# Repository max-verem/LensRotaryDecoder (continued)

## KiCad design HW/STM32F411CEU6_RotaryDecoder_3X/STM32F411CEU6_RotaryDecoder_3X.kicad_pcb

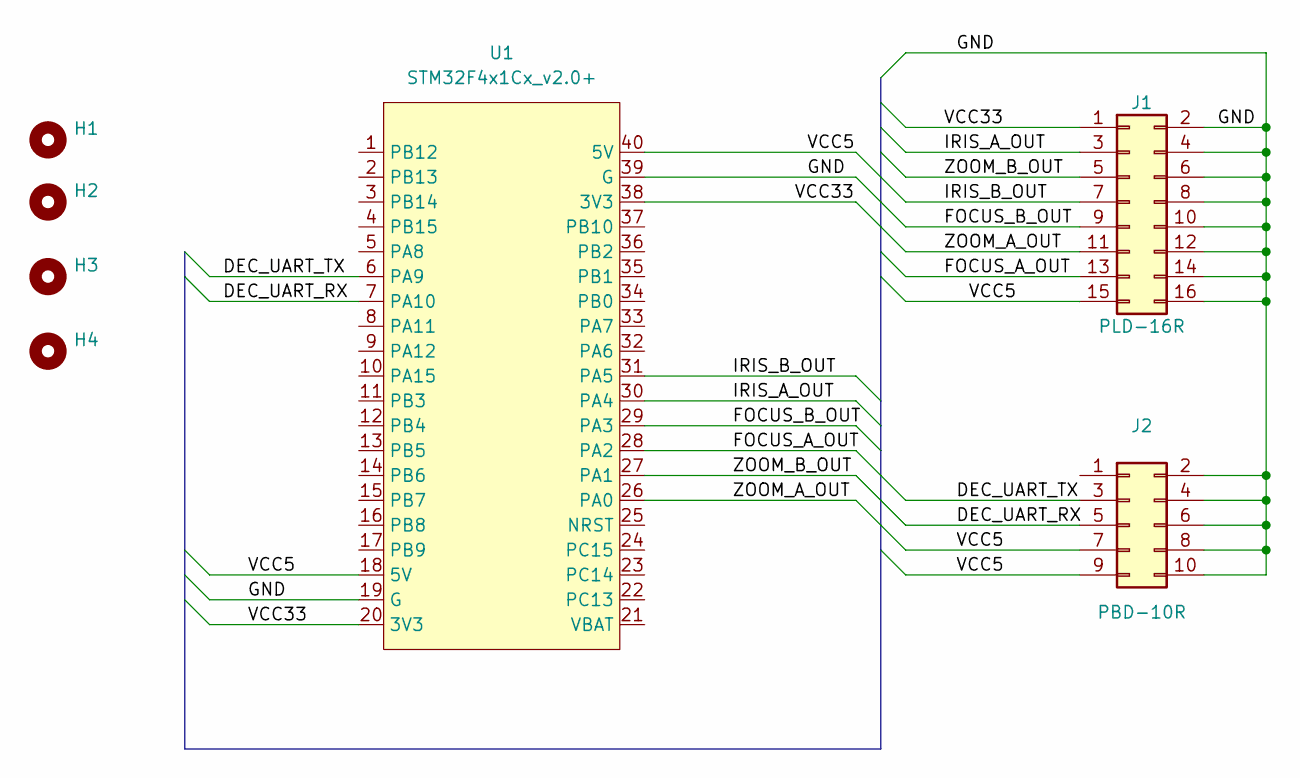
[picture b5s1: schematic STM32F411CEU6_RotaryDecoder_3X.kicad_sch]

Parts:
H1, H2, H3, H4: MountingHole; MountingHole_3.2mm_M3
J1: PLD-16R; PinHeader_2x08_P2.54mm_Horizontal
J2: PBD-10R; PinSocket_2x05_P2.54mm_Horizontal
U1: STM32F4x1Cx_v2.0+; DIP-40_W15.24mm_LongPads

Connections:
/DEC_UART_RX: J2.5, U1.7 (PA10)
/DEC_UART_TX: J2.3, U1.6 (PA9)
/FOCUS_A_OUT: J1.13, U1.28 (PA2)
/FOCUS_B_OUT: J1.9, U1.29 (PA3)
/GND: J1.2, J1.4, J1.6, J1.8, J1.10, J1.12, J1.14, J1.16, J2.2, J2.4, J2.6, J2.8, J2.10, U1.19 (G), U1.39 (G)
/IRIS_A_OUT: J1.3, U1.30 (PA4)
/IRIS_B_OUT: J1.7, U1.31 (PA5)
/VCC5: J1.15, J2.7, J2.9, U1.18 (5V), U1.40 (5V)
/VCC33: J1.1, U1.20 (3V3), U1.38 (3V3)
/ZOOM_A_OUT: J1.11, U1.26 (PA0)
/ZOOM_B_OUT: J1.5, U1.27 (PA1)

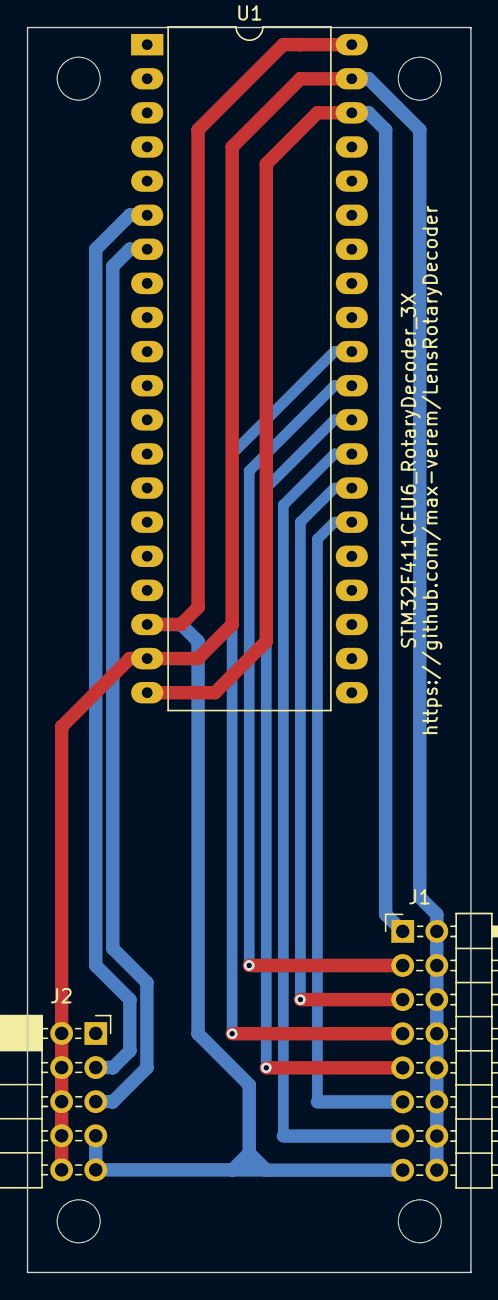
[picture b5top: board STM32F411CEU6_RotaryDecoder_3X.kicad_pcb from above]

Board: 2 copper layers, 33.0 x 92.7 mm, 7 parts (0 on the bottom side), 11 nets.

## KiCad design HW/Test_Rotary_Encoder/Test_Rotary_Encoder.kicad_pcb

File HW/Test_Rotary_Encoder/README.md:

# Test Rotary Encoder

This is a EC11 rotary encoder with debouncing curcuit that is used in this project to debug and simulating purpose.

## Main module

## Schematic

## PCB

gerber [file](gerber/)

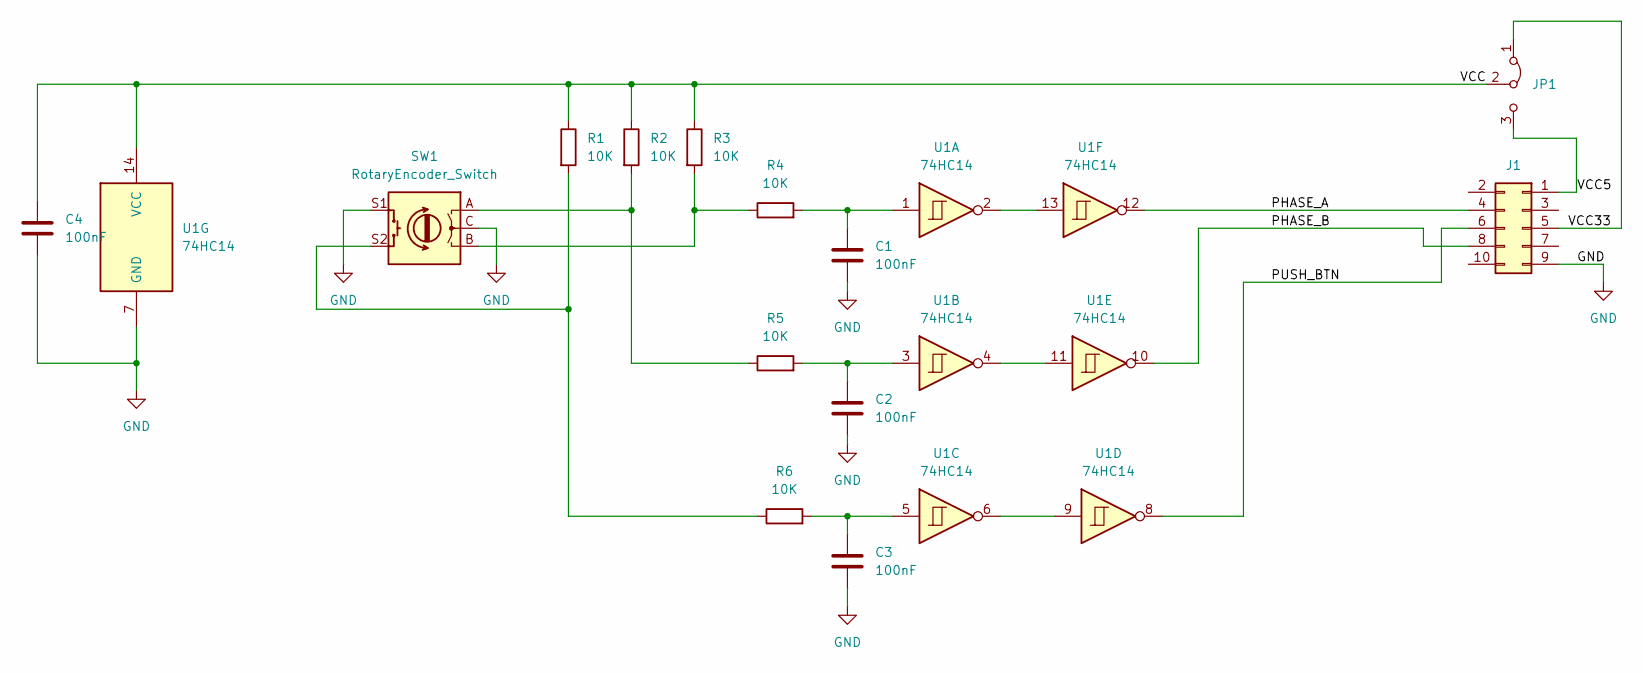
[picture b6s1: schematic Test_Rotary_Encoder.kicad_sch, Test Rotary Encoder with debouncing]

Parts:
C1, C2, C3, C4: 100nF; C_Rect_L7.0mm_W2.0mm_P5.00mm
J1: Conn_02x05_Odd_Even; IDC-Header_2x05_P2.54mm_Vertical
JP1: Jumper_3_Bridged12; PinHeader_1x03_P2.54mm_Vertical
R1, R2, R3, R4, R5, R6: 10K; R_Axial_DIN0309_L9.0mm_D3.2mm_P12.70mm_Horizontal
SW1: RotaryEncoder_Switch; RotaryEncoder_Alps_EC11E-Switch_Vertical_H20mm
U1: 74HC14; DIP-14_W7.62mm

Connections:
/PHASE_A: J1.4, U1.12
/PHASE_B: J1.8, U1.10
/PUSH_BTN: J1.6, U1.8
/VCC: C4.1, JP1.2 (C), R1.1, R2.1, R3.1, U1.14 (VCC)
/VCC5: J1.1, JP1.3 (B)
/VCC33: J1.5, JP1.1 (A)
GND: C1.2, C2.2, C3.2, C4.2, J1.9, SW1.C, SW1.S1, U1.7 (GND)
unnamed: C1.1, R4.2, U1.1
unnamed: C2.1, R5.2, U1.3
unnamed: C3.1, R6.2, U1.5
unnamed: R1.2, R6.1, SW1.S2
unnamed: R2.2, R5.1, SW1.A
unnamed: R3.2, R4.1, SW1.B
unnamed: U1.6, U1.9
unnamed: U1.4, U1.11
unnamed: U1.2, U1.13

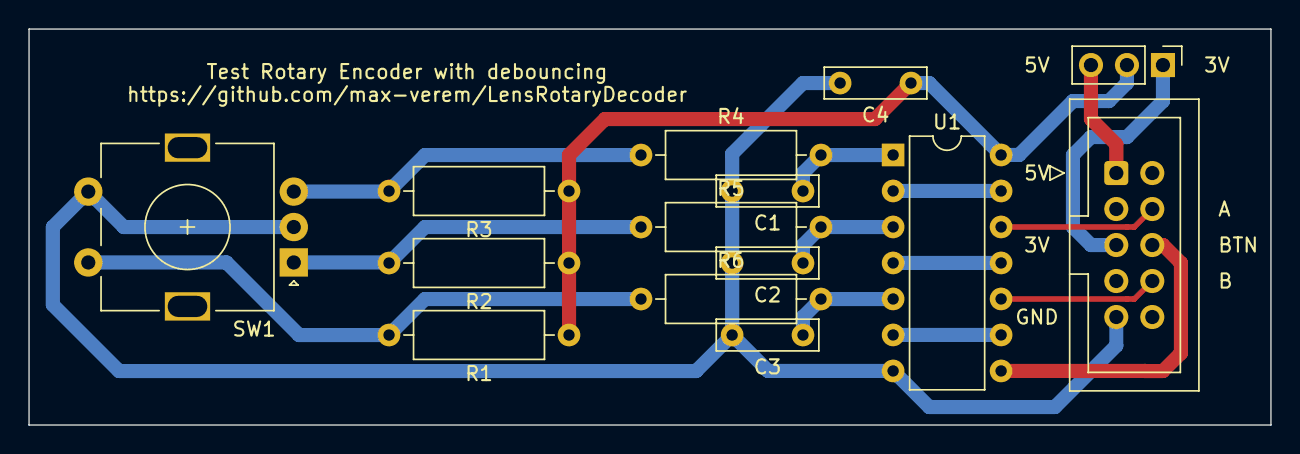
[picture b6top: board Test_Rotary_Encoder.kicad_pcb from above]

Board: 2 copper layers, 87.6 x 27.9 mm, 14 parts (0 on the bottom side), 16 nets.

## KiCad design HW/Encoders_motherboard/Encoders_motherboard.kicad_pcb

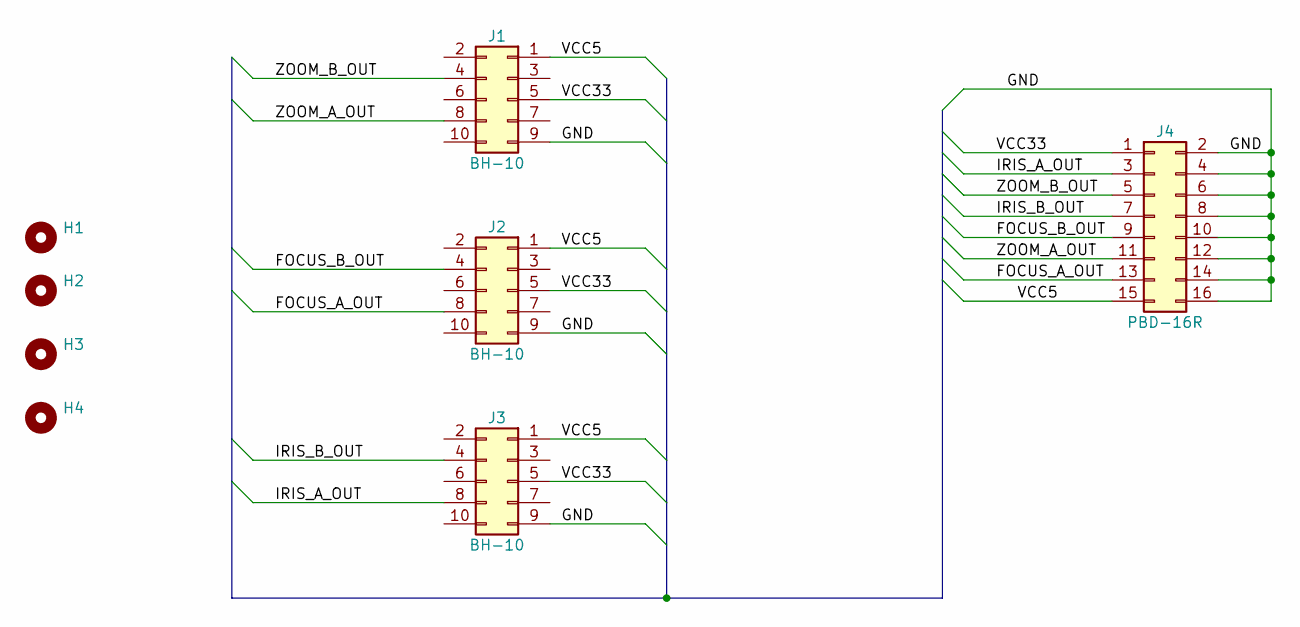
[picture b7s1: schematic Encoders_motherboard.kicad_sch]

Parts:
H1, H2, H3, H4: MountingHole; MountingHole_3.2mm_M3
J1, J2, J3: BH-10; IDC-Header_2x05_P2.54mm_Vertical
J4: PBD-16R; PinSocket_2x08_P2.54mm_Horizontal

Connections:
/FOCUS_A_OUT: J2.8, J4.13
/FOCUS_B_OUT: J2.4, J4.9
/GND: J1.9, J2.9, J3.9, J4.2, J4.4, J4.6, J4.8, J4.10, J4.12, J4.14, J4.16
/IRIS_A_OUT: J3.8, J4.3
/IRIS_B_OUT: J3.4, J4.7
/VCC5: J1.1, J2.1, J3.1, J4.15
/VCC33: J1.5, J2.5, J3.5, J4.1
/ZOOM_A_OUT: J1.8, J4.11
/ZOOM_B_OUT: J1.4, J4.5

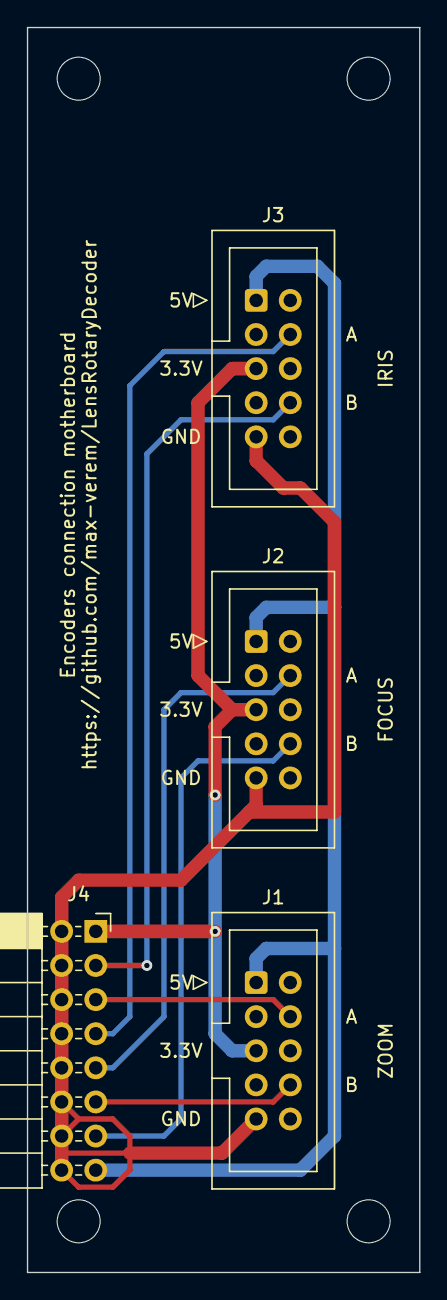
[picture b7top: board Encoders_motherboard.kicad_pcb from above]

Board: 2 copper layers, 29.2 x 92.7 mm, 8 parts (0 on the bottom side), 9 nets.

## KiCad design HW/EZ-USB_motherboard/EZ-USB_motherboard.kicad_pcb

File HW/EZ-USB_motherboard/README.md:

# EZ-USB (CY7C68013A EZ-USB FX2LP) based decoder board for Canon HJ14ex4.3B IRSE 

## Schematic

## PCB

## GERBER
You can download [gerber archive here](gerber/)

## Final board

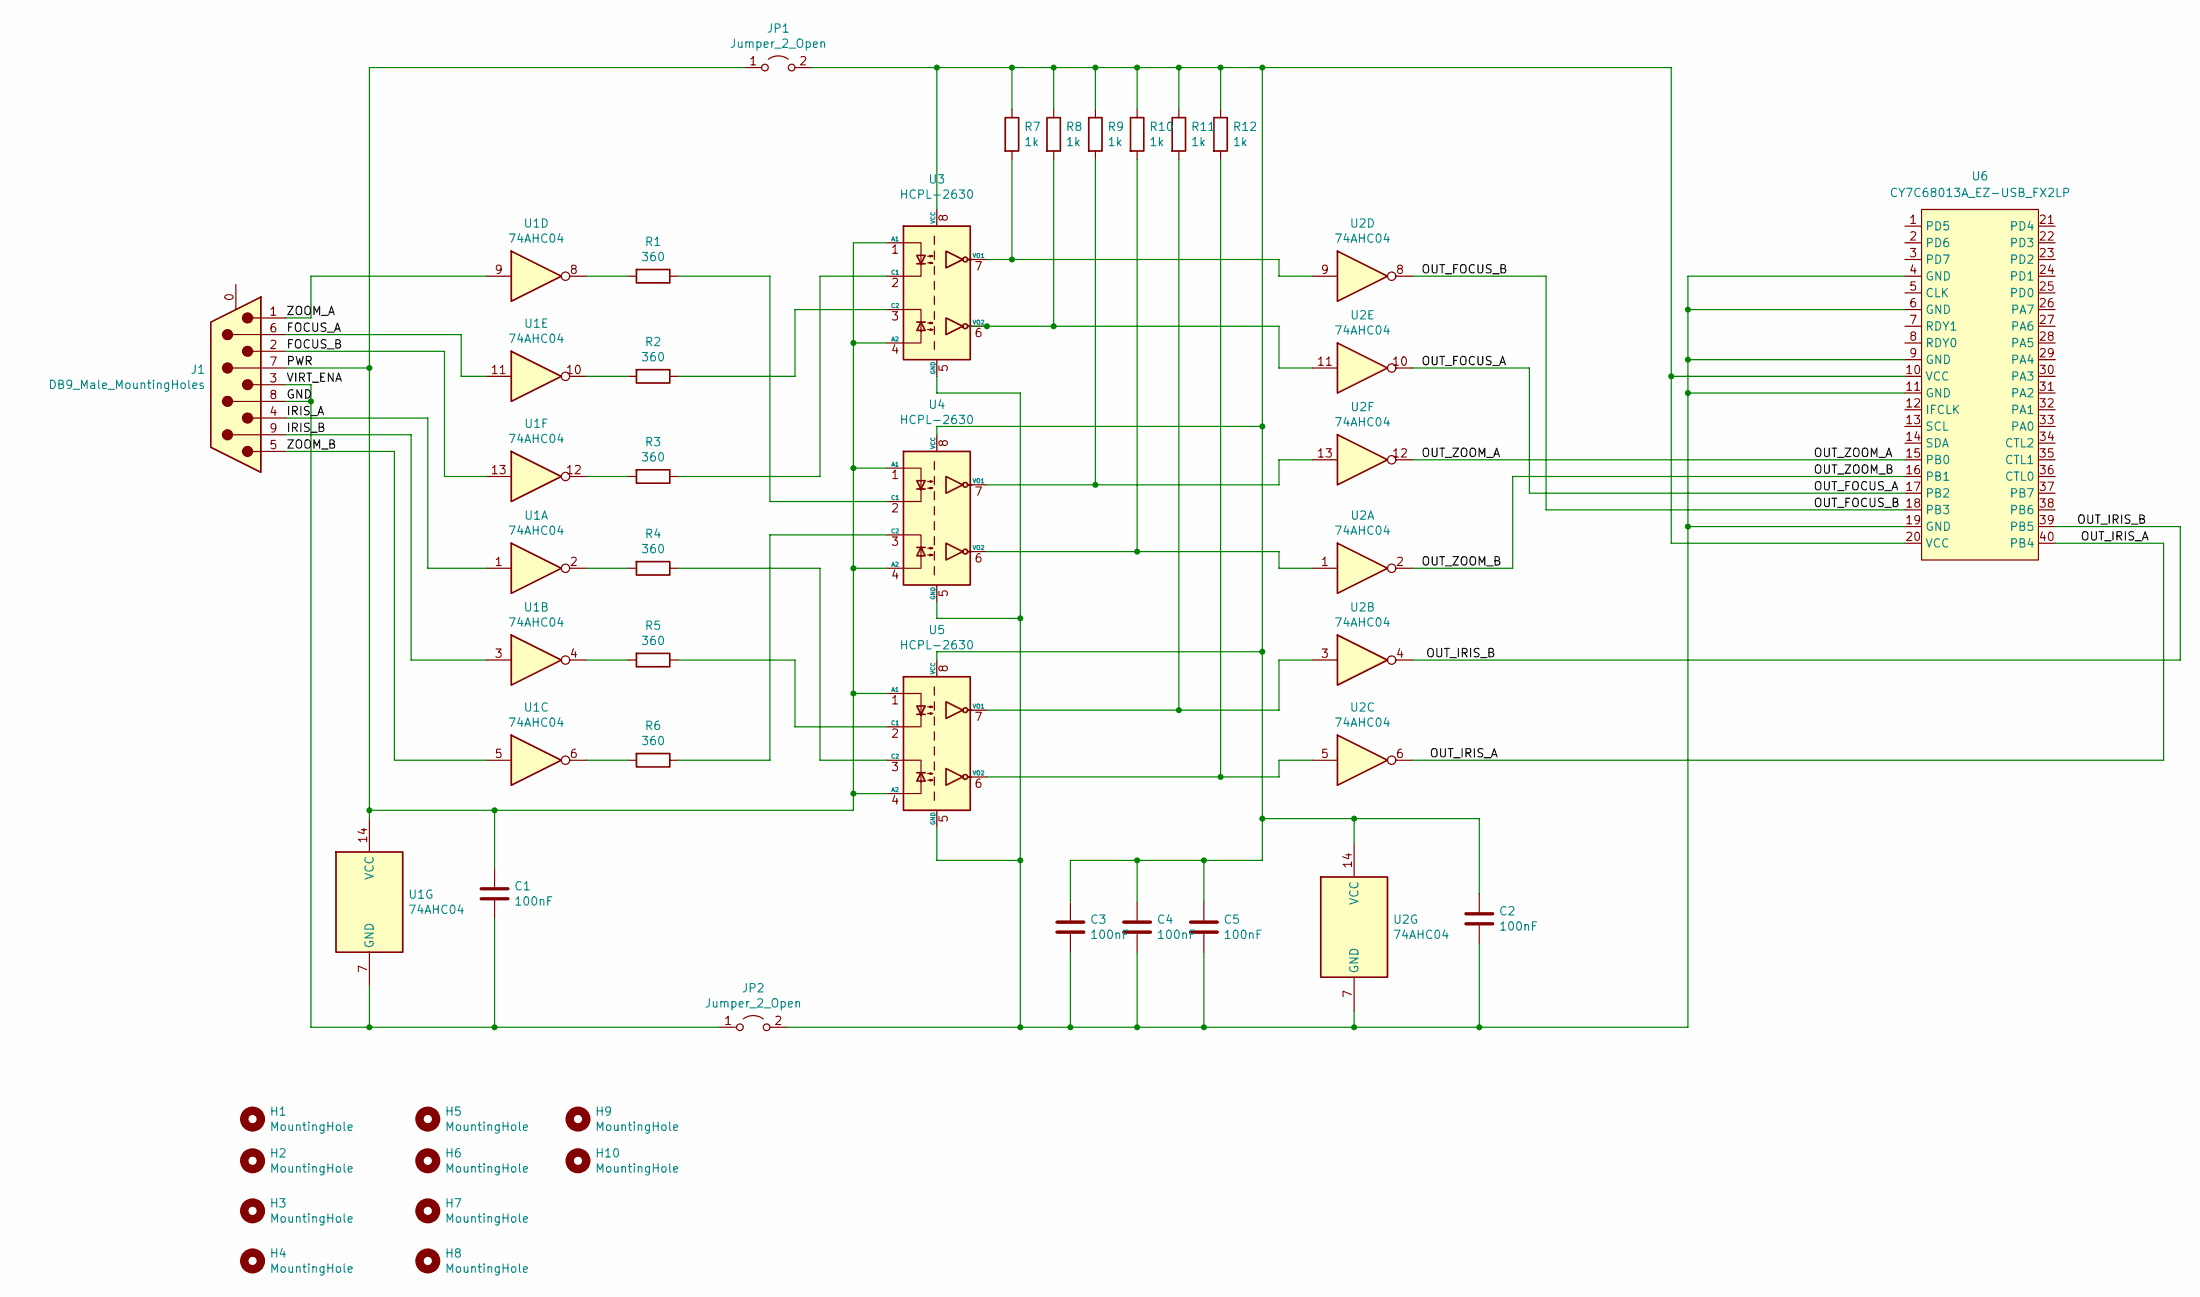
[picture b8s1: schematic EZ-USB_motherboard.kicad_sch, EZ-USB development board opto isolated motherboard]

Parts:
C1, C2, C3, C4, C5: 100nF; C_Rect_L7.0mm_W2.0mm_P5.00mm
H1, H2, H3, H4, H5, H6, H7, H8, H9, H10: MountingHole; MountingHole_3.2mm_M3
J1: DB9_Male_MountingHoles; DSUB-9_Male_Horizontal_P2.77x2.84mm_EdgePinOffset9.90mm_Hou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
JP1, JP2: Jumper_2_Open; PinHeader_1x02_P2.54mm_Vertical
R1, R2, R3, R4, R5, R6: 360; R_Axial_DIN0309_L9.0mm_D3.2mm_P12.70mm_Horizontal
R7, R8, R9, R10, R11, R12: 1k; R_Axial_DIN0309_L9.0mm_D3.2mm_P12.70mm_Horizontal
U1, U2: 74AHC04; DIP-14_W7.62mm
U3, U4, U5: HCPL-2630; DIP-8_W7.62mm
U6: CY7C68013A_EZ-USB_FX2LP

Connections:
/FOCUS_A: J1.6, U1.11
/FOCUS_B: J1.2, U1.13
/GND: C1.2, J1.3, J1.8, JP2.1 (A), U1.7 (GND)
/IRIS_A: J1.4, U1.1
/IRIS_B: J1.9, U1.3
/OUT_FOCUS_A: U2.10, U6.17 (PB2)
/OUT_FOCUS_B: U2.8, U6.18 (PB3)
/OUT_IRIS_A: U2.6, U6.40 (PB4)
/OUT_IRIS_B: U2.4, U6.39 (PB5)
/OUT_ZOOM_A: U2.12, U6.15 (PB0)
/OUT_ZOOM_B: U2.2, U6.16 (PB1)
/PWR: C1.1, J1.7, JP1.1 (A), U1.14 (VCC), U3.1 (A1), U3.4 (A2), U4.1 (A1), U4.4 (A2), U5.1 (A1), U5.4 (A2)
/ZOOM_A: J1.1, U1.9
/ZOOM_B: J1.5, U1.5
unnamed: C2.1, C3.1, C4.1, C5.1, JP1.2 (B), R7.1, R8.1, R9.1, R10.1, R11.1, R12.1, U2.14 (VCC), U3.8 (VCC), U4.8 (VCC), U5.8 (VCC), U6.10 (VCC), U6.20 (VCC)
unnamed: C2.2, C3.2, C4.2, C5.2, JP2.2 (B), U2.7 (GND), U3.5 (GND), U4.5 (GND), U5.5 (GND), U6.4 (GND), U6.6 (GND), U6.9 (GND), U6.11 (GND), U6.19 (GND)
unnamed: R1.1, U4.2 (C1)
unnamed: R1.2, U1.8
unnamed: R2.1, U3.3 (C2)
unnamed: R2.2, U1.10
unnamed: R3.1, U3.2 (C1)
unnamed: R3.2, U1.12
unnamed: R4.1, U5.3 (C2)
unnamed: R4.2, U1.2
unnamed: R5.1, U5.2 (C1)
unnamed: R5.2, U1.4
unnamed: R6.1, U4.3 (C2)
unnamed: R6.2, U1.6
unnamed: R7.2, U2.9, U3.7 (VO1)
unnamed: R8.2, U2.11, U3.6 (VO2)
unnamed: R9.2, U2.13, U4.7 (VO1)
unnamed: R10.2, U2.1, U4.6 (VO2)
unnamed: R11.2, U2.3, U5.7 (VO1)
unnamed: R12.2, U2.5, U5.6 (VO2)

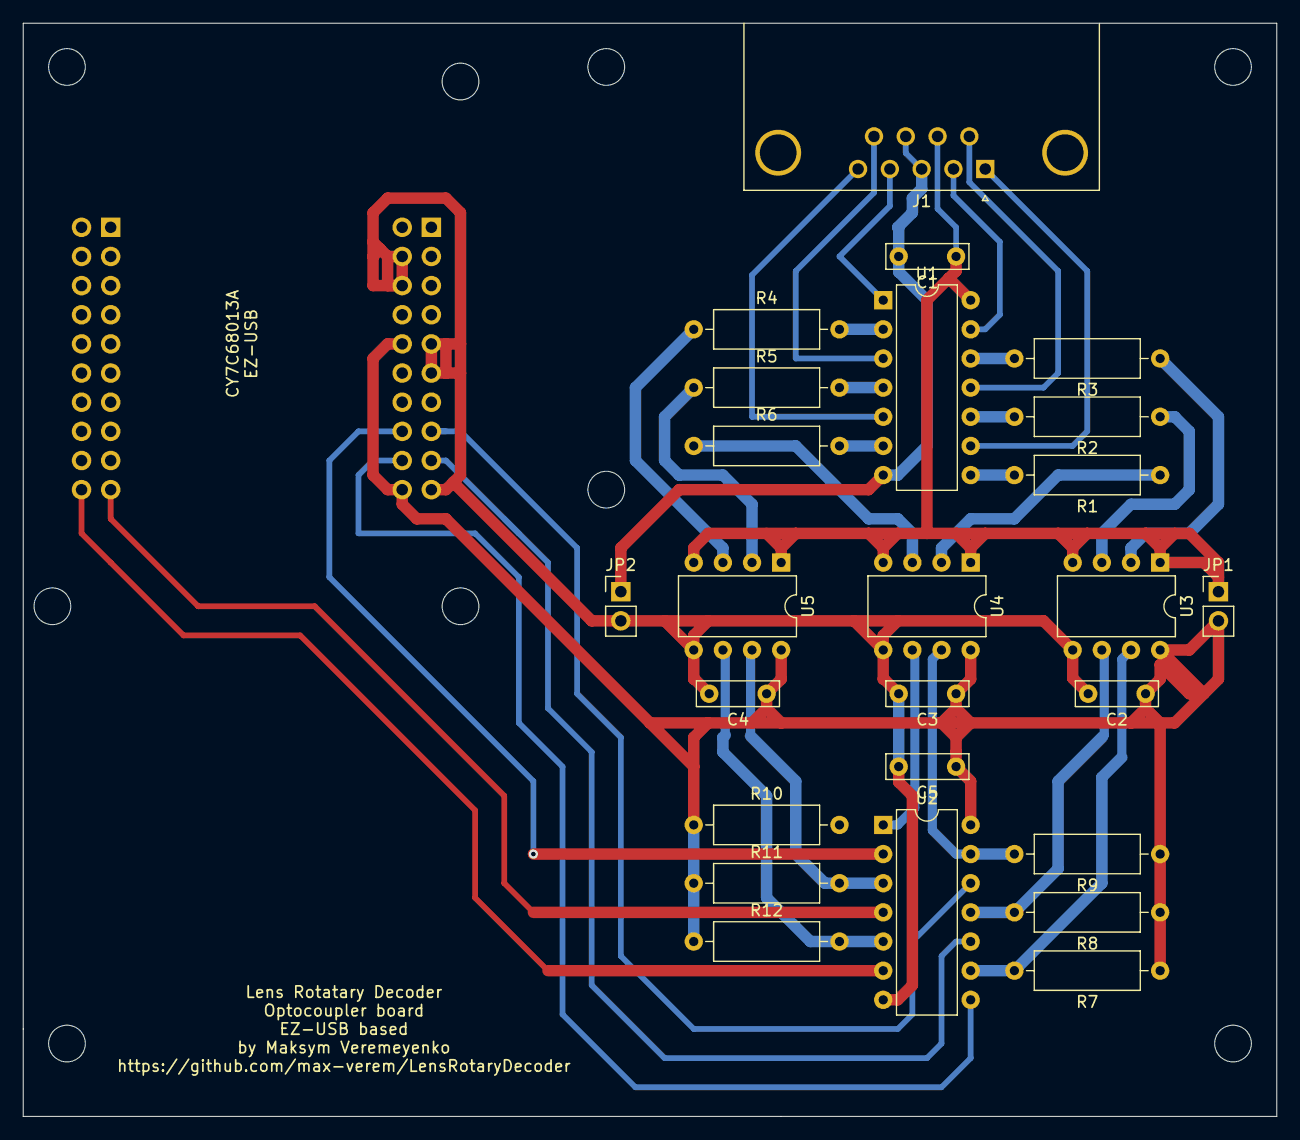
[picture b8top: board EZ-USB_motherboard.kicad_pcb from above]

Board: 2 copper layers, 109.2 x 95.2 mm, 36 parts (1 on the bottom side), 34 nets.

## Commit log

2021-10-12 Initial source code load
2021-10-13 Update CUSTOM_HID_EPIN_SIZE/CUSTOM_HID_EPOUT_SIZE constant to 64
2021-10-13 Update CUSTOM_HID_ReportDesc_FS (reports descriptor)
2021-10-13 Incorporate old working code
2021-10-13 Add .gitignore
2021-10-13 Fix setting initial value byte order
2021-10-13 Clone project for STM32F411CEU6 mcu
2021-10-13 Ignore Debug folder
2021-10-13 Revert byte order change
2021-10-26 FPGA rotary decoder skeleton
2021-12-14 Add EZ-USB rotary decoder skeleton
2021-12-15 Add 'common' code
2021-12-15 Implement minimal reader
2021-12-24 re-implement rotatry decoder
2021-12-24 decoder1 scheme/pcb added
2021-12-24 Re-organize directories for pcb/schematic
2021-12-30 Enable pullup resistors on STM's pins
2021-12-30 add stm32 rotary decoder skeleton
2021-12-30 Implement getting rotary decoder data from STM32 usb dongle
2021-12-30 Update USB VID/PID
2021-12-30 Modify counter/packet length
2022-01-04 MojoV3 serial reader skeleton added
2022-01-04 Implement packet decoder for MojoV3
2022-01-04 FPGA skeleton added
2022-01-04 Basic MojoV3 project added
2022-01-04 Implement static packet serial sender
2022-01-04 Integrate existing Verilog rotary decoder
2022-01-04 Fix byte order
2022-01-04 Integrate EPM570 Verilog code
2022-01-04 Add serial sender module to EPM570 code
2022-01-04 Rename STM32 projects
2022-01-04 Cleanup STM32 projects tree
2022-01-04 Cleanup STM32 projects tree, prepare new project tree
2022-01-04 Add UART code to STM32 project
2022-01-04 Implement serial receive from FPGA, rise frequencies
2022-01-05 uart HAL_Drivers added
2022-01-05 Set 250000 baud output speed for EPM570
2022-01-05 Implement decoding bytestream from EPM570
2022-01-05 Bypass all UART bytestream to HID
2022-01-05 Convert Schematic/PCB to KiCad6.0 format
2022-01-05 Add Kicad-STM32 module for schematic projects
2022-01-05 Camera Lens Cable schematic added
2022-01-05 Update STM32 clock generation config
2022-01-06 Enable timers and dma for futher tests
2022-01-06 Save performance test code
2022-01-06 Rename STM32 project: F411 would be 3X rotation decoder
2022-01-06 Clone and rename stm32_rot_dec into two different reader for compatibility
2022-01-06 rename STM32F103C8_RotaryDecoder to STM32F103C8_RotaryDecoder_1X
2022-01-06 Update Decoders product string
2022-01-06 Fix STM32 decoders projects split
2022-01-06 Cleanup STM32F411CEU6_RotaryDecoder_3X project
2022-01-06 DMA GPIO reading skeleton
2022-01-07 Use DMA2 and TIM1 for getting GPIOA
2022-01-07 Implement getting statistic data
2022-01-07 Test rotary encoder schematic/pcb added
2022-01-07 Update MojoV3's fpga pins for Mojo Hat compatibility
2022-01-11 Implement table based STM32 rotary decoder
2022-01-11 Prevent app crashing after unplug usb dongle
2022-01-11 Cleanup STM32 decoder code, specify constants for table and calc based algorithms
2022-01-12 Initial UART code support added
2022-01-12 Add new modules for STM-UART project
2022-01-13 second OLED display added
2022-01-14 Implement deciminal convertion
2022-01-14 Implement signed/unsigned to decinimal convertion
2022-01-14 I2C to 40000, DMA FIFO, Burst mode
2022-01-14 Sync EZ-USB based decoder to latest version
2022-01-17 UART output startup added
2022-01-17 Rework packet header, enable fifo and burst mode
2022-01-17 Rework packet format
2022-01-17 Sync schematic and pcb with git head
2022-01-18 Restore timer setting throw contstants
2022-01-18 Fix storing status after packet format change
2022-01-18 Link with W5500 library
2022-01-19 UART to NET skeleton
2022-01-19 Minimal UDP sender skeleton for STM32
2022-01-19 Add forgoten files of EPM570 FPGA decoder
2022-01-19 Enable IRQ for UART, setup 230400 baudrate
2022-01-20 Implement Free-D UDP packet sending
2022-01-20 Save some obsolete projects
2022-01-21 Add schematic and pcb of decoder with OLED and NET support
2022-01-21 Enable SPI2 for testing
2022-01-21 Add macros to select SPI used for W5500
2022-01-24 Implement Free-D packet sending
2022-01-25 Fix syncing thread of ez-usb reader
2022-01-25 Add options description for stm32_rot_dec_3x1 reader
2022-01-27 Start documenting camera cable
2022-01-27 Start documenting ez-usb board
2022-01-27 Start documenting EZ-USB based decoder software
2022-01-27 Documenting...
2022-01-27 Save forgoten changes
2022-02-11 Added photo of EZ-USB based device
2022-02-14 Set SO_BROADCAST option to socket
2022-02-17 Move cond var initialization to main
2023-10-15 Rework STM32F411CEU6_FPGA_UART project
2023-10-15 Upgrade project to newer IDE
2023-10-15 Rework STM32F411CEU6_RotaryDecoder_3X project
2025-04-06 Drop old STM32F411CEU6_RotaryDecoder_3X
2025-04-06 Added rotary encoder emulator STM32F411CEU6_RotaryEncoder_3X
2025-04-06 Added updated STM32F411CEU6_RotaryDecoder_3X
2025-04-06 Switch to binary uart packet, build release version
